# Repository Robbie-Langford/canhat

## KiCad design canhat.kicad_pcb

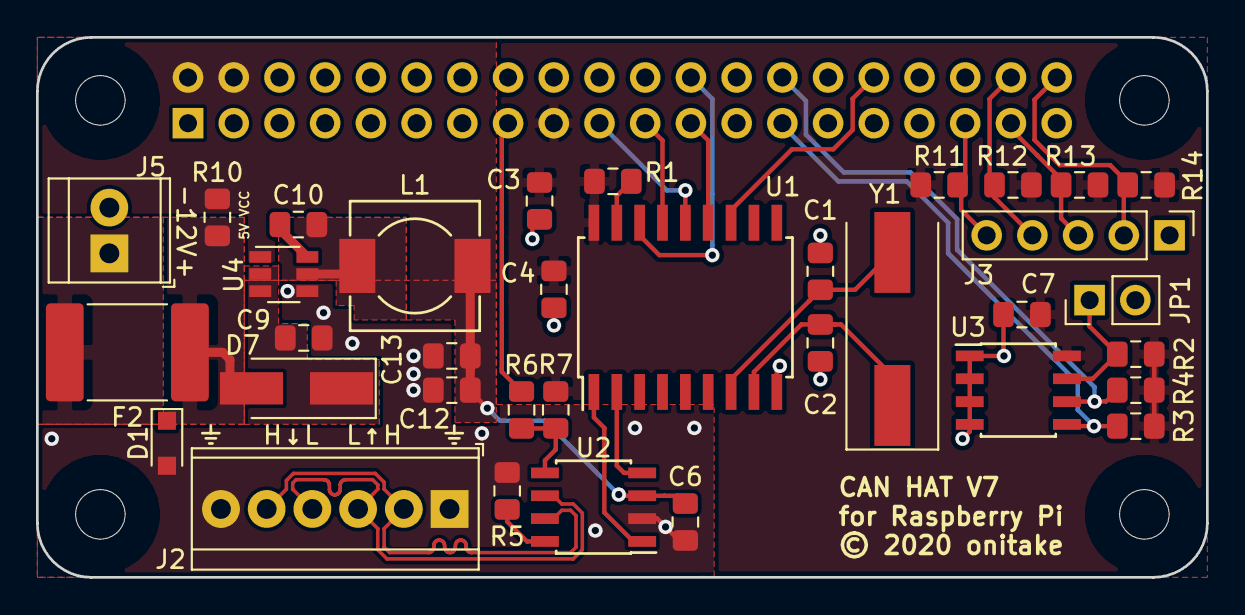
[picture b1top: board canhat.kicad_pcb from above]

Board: 2 copper layers, 65.0 x 30.0 mm, 40 parts (1 on the bottom side), 30 nets.

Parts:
C1, C2: 22p; C_0805_2012Metric_Pad1.15x1.40mm_HandSolder
C3, C9: 10u; C_0805_2012Metric_Pad1.15x1.40mm_HandSolder
C4, C6, C7, C10: 100n; C_0805_2012Metric_Pad1.15x1.40mm_HandSolder
C12, C13: 22u; C_0805_2012Metric_Pad1.15x1.40mm_HandSolder
D1: PESD1IVN24; D_SOD-323_HandSoldering
D7: SS24; D_SMA_Handsoldering
F2: 2920L200; Fuse_2920_7451Metric_Pad2.10x5.45mm_HandSolder
H1: NW; MountingHole_2.7mm
H2: SW; MountingHole_2.7mm
H3: NE; MountingHole_2.7mm
H4: SE; MountingHole_2.7mm
J1: Raspberry_Pi_2_3; PinSocket_2x20_P2.54mm_Vertical
J2: CAN In/Out/GND; TerminalBlock_TE_282834-6_1x06_P2.54mm_Horizontal
J3: GPIO; PinHeader_1x05_P2.54mm_Vertical
J5: 12V; TerminalBlock_TE_282834-2_1x02_P2.54mm_Horizontal
JP1: Write Enable; PinHeader_1x02_P2.54mm_Vertical
L1: 4.7u; DS75LC
R1: 10k; R_0805_2012Metric_Pad1.15x1.40mm_HandSolder
R2, R11, R12, R13, R14: 1k; R_0805_2012Metric_Pad1.15x1.40mm_HandSolder
R3, R4: 3k9; R_0805_2012Metric_Pad1.15x1.40mm_HandSolder
R5, R7: 0; R_0805_2012Metric_Pad1.15x1.40mm_HandSolder
R6: DNP; R_0805_2012Metric_Pad1.15x1.40mm_HandSolder
R10: DNP/0; R_0805_2012Metric_Pad1.15x1.40mm_HandSolder
U1: MCP2515-xSO; SOIC-18W_7.5x11.6mm_P1.27mm
U2: SN65HVDA541; SOIC-8_3.9x4.9mm_P1.27mm
U3: AT24C32-SSHM; SOIC-8_3.9x4.9mm_P1.27mm
U4: AP63205; TSOT-23-6
Y1: 16MHz; Crystal_SMD_HC49-SD

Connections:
+3V3: C3.1, C4.1, C7.1, J1.17, R1.2, R2.1, R3.1, R4.1, R7.1, R11.2, R12.2, R13.2, R14.2, U1.18, U3.8
+5V: C6.1, C12.1, C13.1, J1.2, J1.4, L1.2, R10.1, U2.3, U4.1
+12LF: D1.1, D7.2, F2.2, R10.2
+12V: F2.1, J5.1
/CAN_N: J2.3, J2.4, U2.6
/CAN_P: J2.2, J2.5, U2.7
/GPIO19: J1.35, J3.5, R11.1
/GPIO20: J1.38, J3.4, R12.1
/GPIO21: J1.40, J3.2, R14.1
/GPIO26: J1.37, J3.3, R13.1
/ID_SC: J1.28, R4.2, U3.6
/ID_SD: J1.27, R3.2, U3.5
/MISO: J1.21, U1.15
/MOSI: J1.19, U1.14
/RX: U1.2, U2.4
/SCK: J1.23, U1.13
/TRXEN: J1.15, R6.2
/TX: U1.1, U2.1
/~CS: J1.24, U1.16
/~INT: J1.32, U1.12
GND: C1.2, C2.1, C3.2, C4.2, C6.2, C7.2, C9.2, C12.2, C13.2, D1.2, J1.6, J1.9, J1.14, J1.20, J1.25, J1.30, J1.34, J1.39, J2.1, J2.6, J3.1, J5.2, JP1.2, R5.1, U1.9, U2.2, U3.1, U3.2, U3.3, U3.4, U4.4
unnamed: C1.1, U1.7, Y1.2
unnamed: C2.2, U1.8, Y1.1
unnamed: C9.1, D7.1, U4.2, U4.3
unnamed: C10.1, U4.6
unnamed: C10.2, L1.1, U4.5
unnamed: JP1.1, R2.2, U3.7
unnamed: R1.1, U1.17
unnamed: R5.2, U2.8
unnamed: R6.1, R7.2, U2.5

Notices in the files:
canhat.kicad_pcb:
© 2020 Gregor Riepl
© 2020 onitake
